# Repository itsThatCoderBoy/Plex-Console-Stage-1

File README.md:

# Plex Console Stage 1
## A small devboard that attaches to modules to give endless emulation possibilities!
The way it works is simple: Have the main board, attach it to whatever output device is needed for the game you want to play, and bam! You have a small pocket-sized devboard with endless possibilities of emulation. All you have to do is make your attachment board, code the game, and snap on the main board!\
**This is Stage 1 of this project; it is just the Devboard. After I build this project and it (hopefully) works, I am going to add a case and move on making a tester module.**\
This is my first project as part of Hack Club, and I certainly hope it isn't my last! This has already been so fun, even just a couple hours in.

## Why & How
This project came about because i really liked Bitluni's Megaplex video (oh boy I wonder where the name came from), and I wanted to make something inspired by it.\
I initially was thinking of doing something exactly like his, but then realised that that would be a bad idea, and so I decided to make it my own by adding:
 - Different battery (rechargable!)
 - Modular snap-on system
 - Completely different display (ok this is an entirely different thing)

Thank you so much to Hack Club and Forge for making this whole thing possible! This really is an amazing oppurtunity.

## What is it?
This project firstly involves a devboard. The reason it isn't a single board with the I/O and everything is because the main devboard is one of the more expensive things (~$35-40 including shipping for components), and I wanted you to just have one for all of the possible modules. (Also because I wanted a concrete starting point)\
**Note: This is a test for just the devboard. I am going to make a case and print it myself when I have confirmation that it works and I will be able to measure something concrete. Also, the 3D model on KiCad is missing quite a few componenets and I am going to need those in order to make a good case.**\
The second part of the project is the modules. They snap onto the devboard with magnets and communicate with pads on the back of both. Modules can do anything, as long as you code it right and have enough I/O pins!

## What's the Plan?
I currently have the devboard designed and ready to ship off to JLCPCB when I get funding!\
The first module that I am going to create is just a simple screen made of Charlie-Plexed LEDS. This is mainly just to practice coding, get the connection between the devboard and module hammered down, and make sure that the devboard works of course.\
After that, I move on to the main idea: The Nintendon't GameMan. This is basically a Gameboy-like little pocket console with famous games like Tesris, Pac-Boy, and maybe even Toader! I haven't gotten to this point yet of course, but I am moving swiftly along.
Last but not least, if I have any extra time, I'd eventually like to make other attachments (feel free to leave suggestions).

## Current Progress:

### *Devboard*
*Schematic*\

*PCB Layout*\

*Built-in KiCad 3D Model Front*\

*Build Photo*

## BOM

## Build

[View my project timeline on Lapse](https://lapse.hackclub.com/user/@itsthatcoderboy)

https://github.com/user-attachments/assets/fe2d55e1-1f7b-49ab-ab0b-663dc05e2e7f

https://github.com/user-attachments/assets/89aea018-e0ea-4a9d-9f60-57c4afef2afe

https://github.com/user-attachments/assets/4f556e5a-54bf-4c0b-9238-5e6fd982241c

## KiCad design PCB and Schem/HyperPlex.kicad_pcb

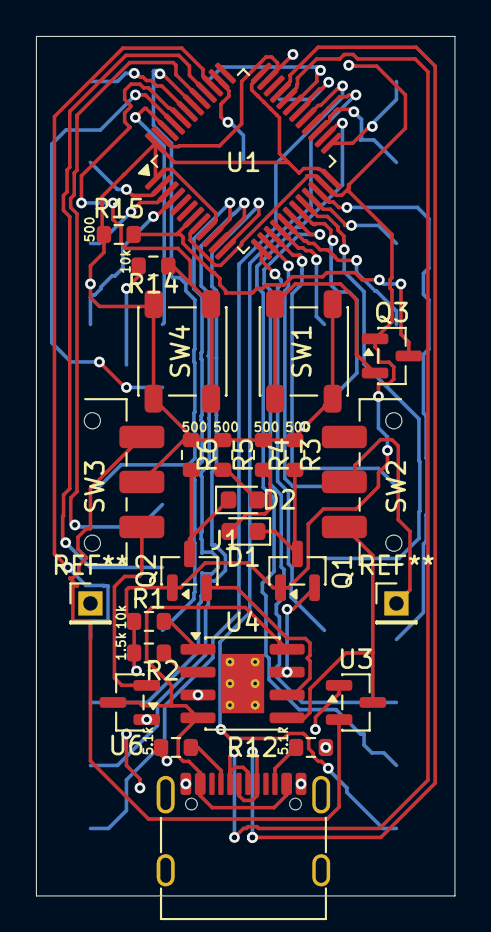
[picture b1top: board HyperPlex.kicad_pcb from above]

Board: 2 copper layers, 23.2 x 47.8 mm, 25 parts (1 on the bottom side), 21 nets.

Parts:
D1, D2: LED; D_0603_1608Metric
HyperPlex: HyperPlex Connector
J1: USB_C_Receptacle_USB2.0_16P; USB_C_Receptacle_G-Switch_GT-USB-7010ASV
Q1, Q2, Q3: 2N3904; SOT-23
R1, R14: 10k; R_0603_1608Metric
R2: 1.5k; R_0603_1608Metric
R3, R4, R5, R6, R15: 500; R_0603_1608Metric
R12, R13: 5.1k; R_0603_1608Metric
SW1, SW4: SW_Push; SW_SPST_PTS647_Sx38
SW2, SW3: SW_SPDT; SW_SPDT_CK_JS102011SAQN
U1: CH32V203CxTx; LQFP-48_7x7mm_P0.5mm
U3, U6: XC6206PxxxMR; SOT-23
U4: TP4056-42-ESOP8; SOIC-8-1EP_3.9x4.9mm_P1.27mm_EP2.41x3.3mm_ThermalVias

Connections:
/3.3V: HyperPlex.3.3V, R3.1, R4.1, R5.1, R6.1, R15.1, SW1.2, SW3.2 (B), SW4.1, U1.1 (VBAT), U1.9 (VDDA), U1.24 (VDD_VIO), U1.36 (VDD), U1.48 (VDD)
/3.3VRAW: SW2.1 (A), U3.3 (VI), U4.5 (BAT)
/RST: Q3.3 (C), R15.2, U1.7 (~RST)
/USB5V: J1.A4 (VBUS), J1.A9 (VBUS), J1.B4 (VBUS), J1.B9 (VBUS), U4.4 (V_{CC}), U4.8 (CE), U6.3 (VI)
/USBDN: J1.A7 (D-), J1.B7 (D-), U1.32 (PA11)
/USBDP: J1.A6 (D+), J1.B6 (D+), U1.33 (PA12)
GND: HyperPlex.GND, J1.A1 (GND), J1.A12 (GND), J1.B1 (GND), J1.B12 (GND), J1.SH (SHIELD), Q1.1 (E), Q2.1 (E), Q3.1 (E), R1.2, R2.2, R12.2, R13.2, R14.1, U1.8 (VSSA), U1.23 (VSS), U1.35 (VSS), U1.47 (VSS), U3.1 (GND), U4.3 (GND), U4.9 (EPAD), U6.1 (GND)
unnamed: D1.2 (A), R4.2
unnamed: D1.1 (K), Q1.3 (C), R3.2
unnamed: D2.2 (A), R5.2
unnamed: D2.1 (K), Q2.3 (C), R6.2
unnamed: J1.A5 (CC1), R13.1
unnamed: J1.B5 (CC2), R12.1
unnamed: Q1.2 (B), U4.7 (~CHRG)
unnamed: Q2.2 (B), U4.6 (~STDBY)
unnamed: Q3.2 (B), SW1.1
unnamed: SW3.1 (A), U3.2 (VO)
unnamed: SW3.3 (C), U6.2 (VO)
unnamed: R14.2, SW4.2, U1.44 (BOOT0)
unnamed: R2.1, U4.2 (PROG)
unnamed: R1.1, U4.1 (TEMP)
